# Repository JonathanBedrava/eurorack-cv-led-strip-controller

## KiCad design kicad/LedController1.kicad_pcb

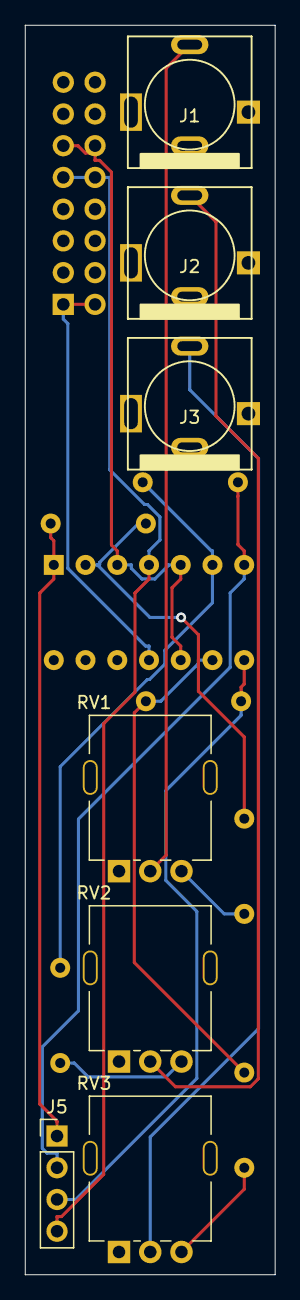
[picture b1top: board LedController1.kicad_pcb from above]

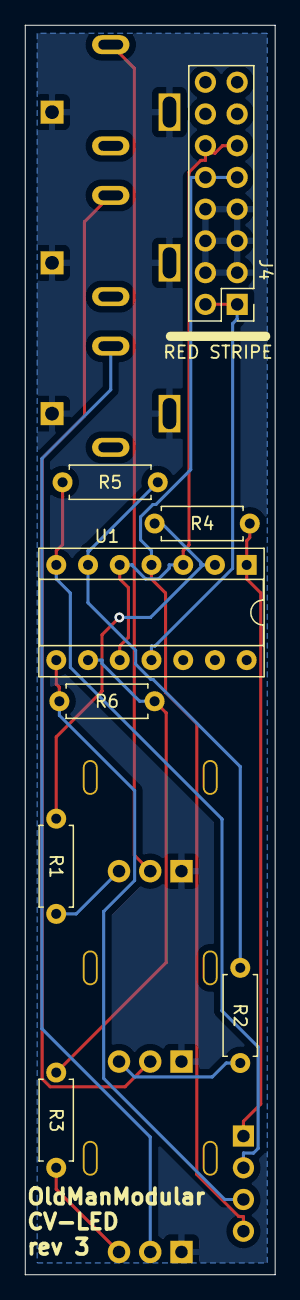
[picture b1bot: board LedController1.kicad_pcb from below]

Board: 2 copper layers, 20.0 x 100.0 mm, 15 parts (8 on the bottom side), 16 nets.

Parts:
J1, J2, J3: AudioJack2; PJ301BM
J4: Conn_02x08_Odd_Even; PinHeader_2x08_P2.54mm_Vertical
J5: Conn_01x04_Female; PinHeader_1x04_P2.54mm_Vertical
R1, R2, R3: 10K; R_Axial_DIN0207_L6.3mm_D2.5mm_P7.62mm_Horizontal
R4, R5, R6: 22K; R_Axial_DIN0207_L6.3mm_D2.5mm_P7.62mm_Horizontal
RV1, RV2, RV3: 100K; Potentiometer_Alpha_Single_Vertical
U1: TL084; DIP-14_W7.62mm_Socket

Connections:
+5V: J4.11, J4.12, U1.3 (+), U1.5 (+), U1.10 (+)
+12V: J4.9, J4.10, J5.4, U1.4 (V+)
-12V: J4.1, J4.2, U1.11 (V-)
/InputSignal/Signal: R1.2, RV1.3
/sheet5FE67A34/Signal: R3.2, RV3.3
/sheet5FE679DC/Signal: R2.2, RV2.3
GND: J1.S, J2.S, J3.S, J4.3, J4.4, J4.5, J4.6, J4.7, J4.8, RV1.1, RV2.1, RV3.1
unnamed: J1.T, RV1.2
unnamed: J2.T, RV2.2
unnamed: J3.T, RV3.2
unnamed: J5.1, R4.2, U1.1
unnamed: J5.2, R5.2, U1.7
unnamed: J5.3, R6.2, U1.8
unnamed: R1.1, R4.1, U1.2 (-)
unnamed: R2.1, R5.1, U1.6 (-)
unnamed: R3.1, R6.1, U1.9 (-)

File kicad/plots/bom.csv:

Comment,Designator,Footprint,LCSC
"AudioJack2","J1,J2,J3","SynthDiyFootprintLibrary:PJ301BM",""
"EURO_PWR_2x5-eurocad-euro_pwr_2x5-eurocad","J4","Connector_PinHeader_2.54mm:PinHeader_2x08_P2.54mm_Vertical",""
"Conn_01x04_Female","J5","Connector_PinHeader_2.54mm:PinHeader_1x04_P2.54mm_Vertical",""
"10K","R1,R2,R3","Resistor_SMD:R_1206_3216Metric",""
"22K","R4,R5,R6","Resistor_SMD:R_1206_3216Metric",""
"100K","RV1,RV2,RV3","Potentiometer_THT:Potentiometer_Alpha_RD901F-40-00D_Single_Vertical",""
"TL084","U1","Package_SO:SOIC-14_3.9x8.7mm_P1.27mm",""

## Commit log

2021-01-08 Adding kicad project
2021-01-08 Changing dir structure
2021-07-04 Adding plots for JLCPCB
2021-07-04 Renaming folder
2021-07-04 Renaming plots forlder for 3x version
2022-02-23 Correcting PJ301BM footprint
